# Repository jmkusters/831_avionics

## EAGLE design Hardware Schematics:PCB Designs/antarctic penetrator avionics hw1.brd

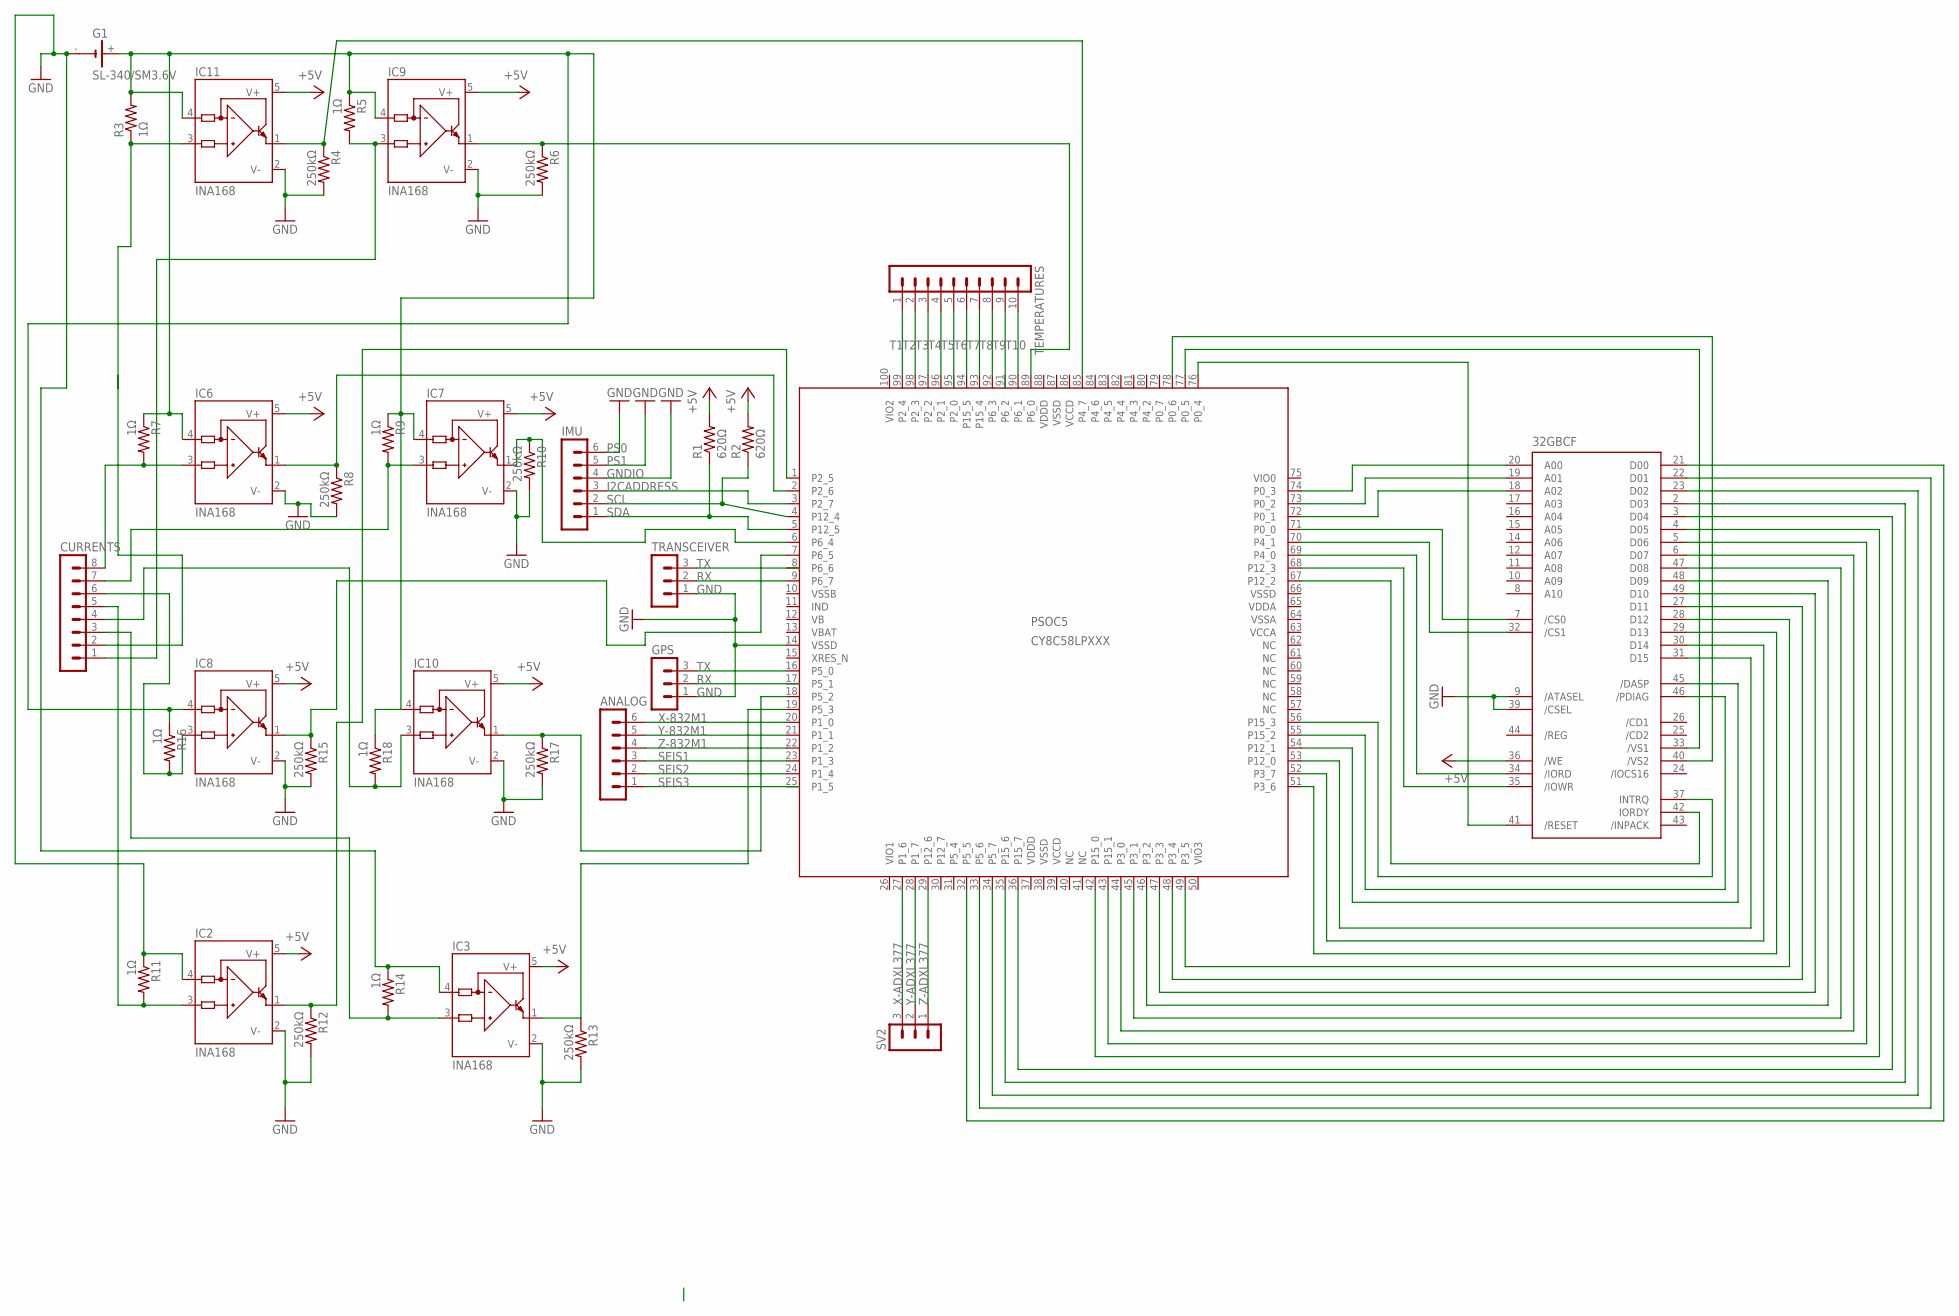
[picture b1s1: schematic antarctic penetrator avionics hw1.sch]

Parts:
32GBCF: CF-CARD-IDE_MODE; MI20-50PD-SF
ANALOG: MA06-1
CURRENTS: MA08-1
G1: SL-340/SM3.6V
GPS: MA03-1
IC2, IC3, IC6, IC7, IC8, IC9, IC10, IC11: INA168; SOT23-5
IMU: MA06-1
PSOC5: CY8C58LPXXX; TQFP100-14X14
R1, R2: 620Ω; 0204/5
R3, R5, R7, R9, R11, R14, R16, R18: 1Ω; 0204/5
R4, R6, R8, R10, R12, R13, R15, R17: 250kΩ; 0204/5
SV2: MA03-1
TEMPERATURES: MA10-1
TRANSCEIVER: MA03-1

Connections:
+5V: 32GBCF.36 (/WE), IC2.5 (V+), IC3.5 (V+), IC6.5 (V+), IC7.5 (V+), IC8.5 (V+), IC9.5 (V+), IC10.5 (V+), IC11.5 (V+), R1.2, R2.2
GND: 32GBCF.9 (/ATASEL), 32GBCF.39 (/CSEL), G1.-, GPS.1, IC2.2 (V-), IC2.4 (IN-), IC3.2 (V-), IC3.4 (IN-), IC6.2 (V-), IC7.2 (V-), IC8.2 (V-), IC9.2 (V-), IC10.2 (V-), IC11.2 (V-), PSOC5.14 (VSSD), R4.2, R6.2, R8.2, R10.2, R11.1, R12.2, R13.2, R14.1, R15.2, R17.2, TRANSCEIVER.1
GND1: 32GBCF.1 (GND1)
GND2: 32GBCF.50 (GND2)
GNDIO: IMU.4
I2CADDRESS: IMU.3, PSOC5.3 (P2_7)
unnamed: IC9.1 (OUT), PSOC5.89 (P6_0), R6.1
unnamed: IC11.1 (OUT), PSOC5.85 (P4_7), R4.1
unnamed: 32GBCF.41 (/RESET), PSOC5.76 (P0_4)
unnamed: CURRENTS.6, IC8.3 (IN+), R16.2
unnamed: CURRENTS.7, IC7.3 (IN+), R9.2
unnamed: CURRENTS.8, IC6.3 (IN+), R7.2
unnamed: CURRENTS.5, IC2.3 (IN+), R11.2
unnamed: CURRENTS.4, IC10.3 (IN+), R18.2
unnamed: CURRENTS.3, IC3.3 (IN+), R14.2
unnamed: CURRENTS.2, IC11.3 (IN+), R3.1
unnamed: 32GBCF.33 (/VS1), PSOC5.77 (P0_5)
unnamed: IC9.3 (IN+), R5.2
unnamed: 32GBCF.40 (/VS2), PSOC5.78 (P0_6)
unnamed: IC10.1 (OUT), PSOC5.18 (P5_2), R17.1
unnamed: IC3.1 (OUT), PSOC5.19 (P5_3)
unnamed: IC7.1 (OUT), PSOC5.6 (P6_4), R10.1
unnamed: IC6.1 (OUT), PSOC5.2 (P2_6), R8.1
unnamed: IC8.1 (OUT), PSOC5.7 (P6_5), R15.1
unnamed: IC2.1 (OUT), PSOC5.1 (P2_5), R12.1
unnamed: 32GBCF.20 (A00), PSOC5.74 (P0_3)
unnamed: 32GBCF.19 (A01), PSOC5.73 (P0_2)
unnamed: 32GBCF.18 (A02), PSOC5.72 (P0_1)
unnamed: 32GBCF.7 (/CS0), PSOC5.71 (P0_0)
unnamed: 32GBCF.32 (/CS1), PSOC5.70 (P4_1)
unnamed: 32GBCF.34 (/IORD), PSOC5.69 (P4_0)
unnamed: 32GBCF.35 (/IOWR), PSOC5.68 (P12_3)
unnamed: 32GBCF.42 (IORDY), PSOC5.67 (P12_2)
unnamed: 32GBCF.37 (INTRQ), PSOC5.56 (P15_3)
unnamed: 32GBCF.46 (/PDIAG), PSOC5.55 (P15_2)
unnamed: 32GBCF.45 (/DASP), PSOC5.54 (P12_1)
unnamed: 32GBCF.31 (D15), PSOC5.53 (P12_0)
unnamed: 32GBCF.30 (D14), PSOC5.52 (P3_7)
unnamed: 32GBCF.29 (D13), PSOC5.51 (P3_6)
unnamed: 32GBCF.28 (D12), PSOC5.49 (P3_5)
unnamed: 32GBCF.27 (D11), PSOC5.48 (P3_4)
unnamed: 32GBCF.49 (D10), PSOC5.47 (P3_3)
unnamed: 32GBCF.48 (D09), PSOC5.46 (P3_2)
unnamed: 32GBCF.47 (D08), PSOC5.45 (P3_1)
unnamed: 32GBCF.6 (D07), PSOC5.44 (P3_0)
unnamed: 32GBCF.5 (D06), PSOC5.43 (P15_1)
unnamed: 32GBCF.4 (D05), PSOC5.42 (P15_0)
unnamed: 32GBCF.3 (D04), PSOC5.36 (P15_7)
unnamed: 32GBCF.2 (D03), PSOC5.35 (P15_6)
unnamed: 32GBCF.23 (D02), PSOC5.34 (P5_7)
unnamed: 32GBCF.22 (D01), PSOC5.33 (P5_6)
unnamed: 32GBCF.21 (D00), PSOC5.32 (P5_5)
unnamed: G1.+, IC6.4 (IN-), IC7.4 (IN-), IC8.4 (IN-), IC9.4 (IN-), IC10.4 (IN-), IC11.4 (IN-), R3.2, R5.1, R7.1, R9.1, R16.1, R18.1
PS0: IMU.6
PS1: IMU.5
RX: GPS.2, PSOC5.9 (P6_7), TRANSCEIVER.2
SCL: IMU.2, PSOC5.4 (P12_4), R2.1
SDA: IMU.1, PSOC5.5 (P12_5), R1.1
SEIS1: ANALOG.3, PSOC5.23 (P1_3)
SEIS2: ANALOG.2, PSOC5.24 (P1_4)
SEIS3: ANALOG.1
T1: PSOC5.99 (P2_4), TEMPERATURES.1
T2: PSOC5.98 (P2_3), TEMPERATURES.2
T3: PSOC5.97 (P2_2), TEMPERATURES.3
T4: PSOC5.96 (P2_1), TEMPERATURES.4
T5: TEMPERATURES.5
T6: PSOC5.94 (P15_5), TEMPERATURES.6
T7: PSOC5.93 (P15_4), TEMPERATURES.7
T8: PSOC5.92 (P6_3), TEMPERATURES.8
T9: TEMPERATURES.9
T10: PSOC5.90 (P6_1), TEMPERATURES.10
TX: GPS.3, PSOC5.16 (P5_0), TRANSCEIVER.3
VCC1: 32GBCF.38 (VCC1)
VCC2: 32GBCF.13 (VCC2)
VCCA: PSOC5.63 (VCCA)
VCCD: PSOC5.39 (VCCD), PSOC5.86 (VCCD)
VDDA: PSOC5.65 (VDDA)
VDDD: PSOC5.37 (VDDD), PSOC5.88 (VDDD)
VSSA: PSOC5.64 (VSSA)
VSSB: PSOC5.10 (VSSB)
VSSD: PSOC5.38 (VSSD), PSOC5.66 (VSSD), PSOC5.87 (VSSD)
X-832M1: ANALOG.6, PSOC5.20 (P1_0)
X-ADXL377: PSOC5.27 (P1_6), SV2.3
Y-832M1: ANALOG.5, PSOC5.21 (P1_1)
Y-ADXL377: PSOC5.28 (P1_7), SV2.2
Z-832M1: ANALOG.4, PSOC5.22 (P1_2)
Z-ADXL377: PSOC5.29 (P12_6), SV2.1

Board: 2 copper layers, 36 parts (0 on the bottom side), 73 nets, no tracks yet.

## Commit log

2016-02-20 Adding schematics, datasheets, and block diagrams from 83
2016-02-20 changing name and adding current shunt diagram
2016-02-20 updating on windows
2016-02-25 initial psoc project commit
